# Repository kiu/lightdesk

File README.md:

# lightdesk

Custom desk light and RGB strip controller

Superseded by [https://github.com/kiu/kha](https://github.com/kiu/kha)

## Photos

## Render

# License

This project is licensed under the Creative Commons Attribution-NonCommercial 3.0 Unported (CC BY-NC 3.0) license.

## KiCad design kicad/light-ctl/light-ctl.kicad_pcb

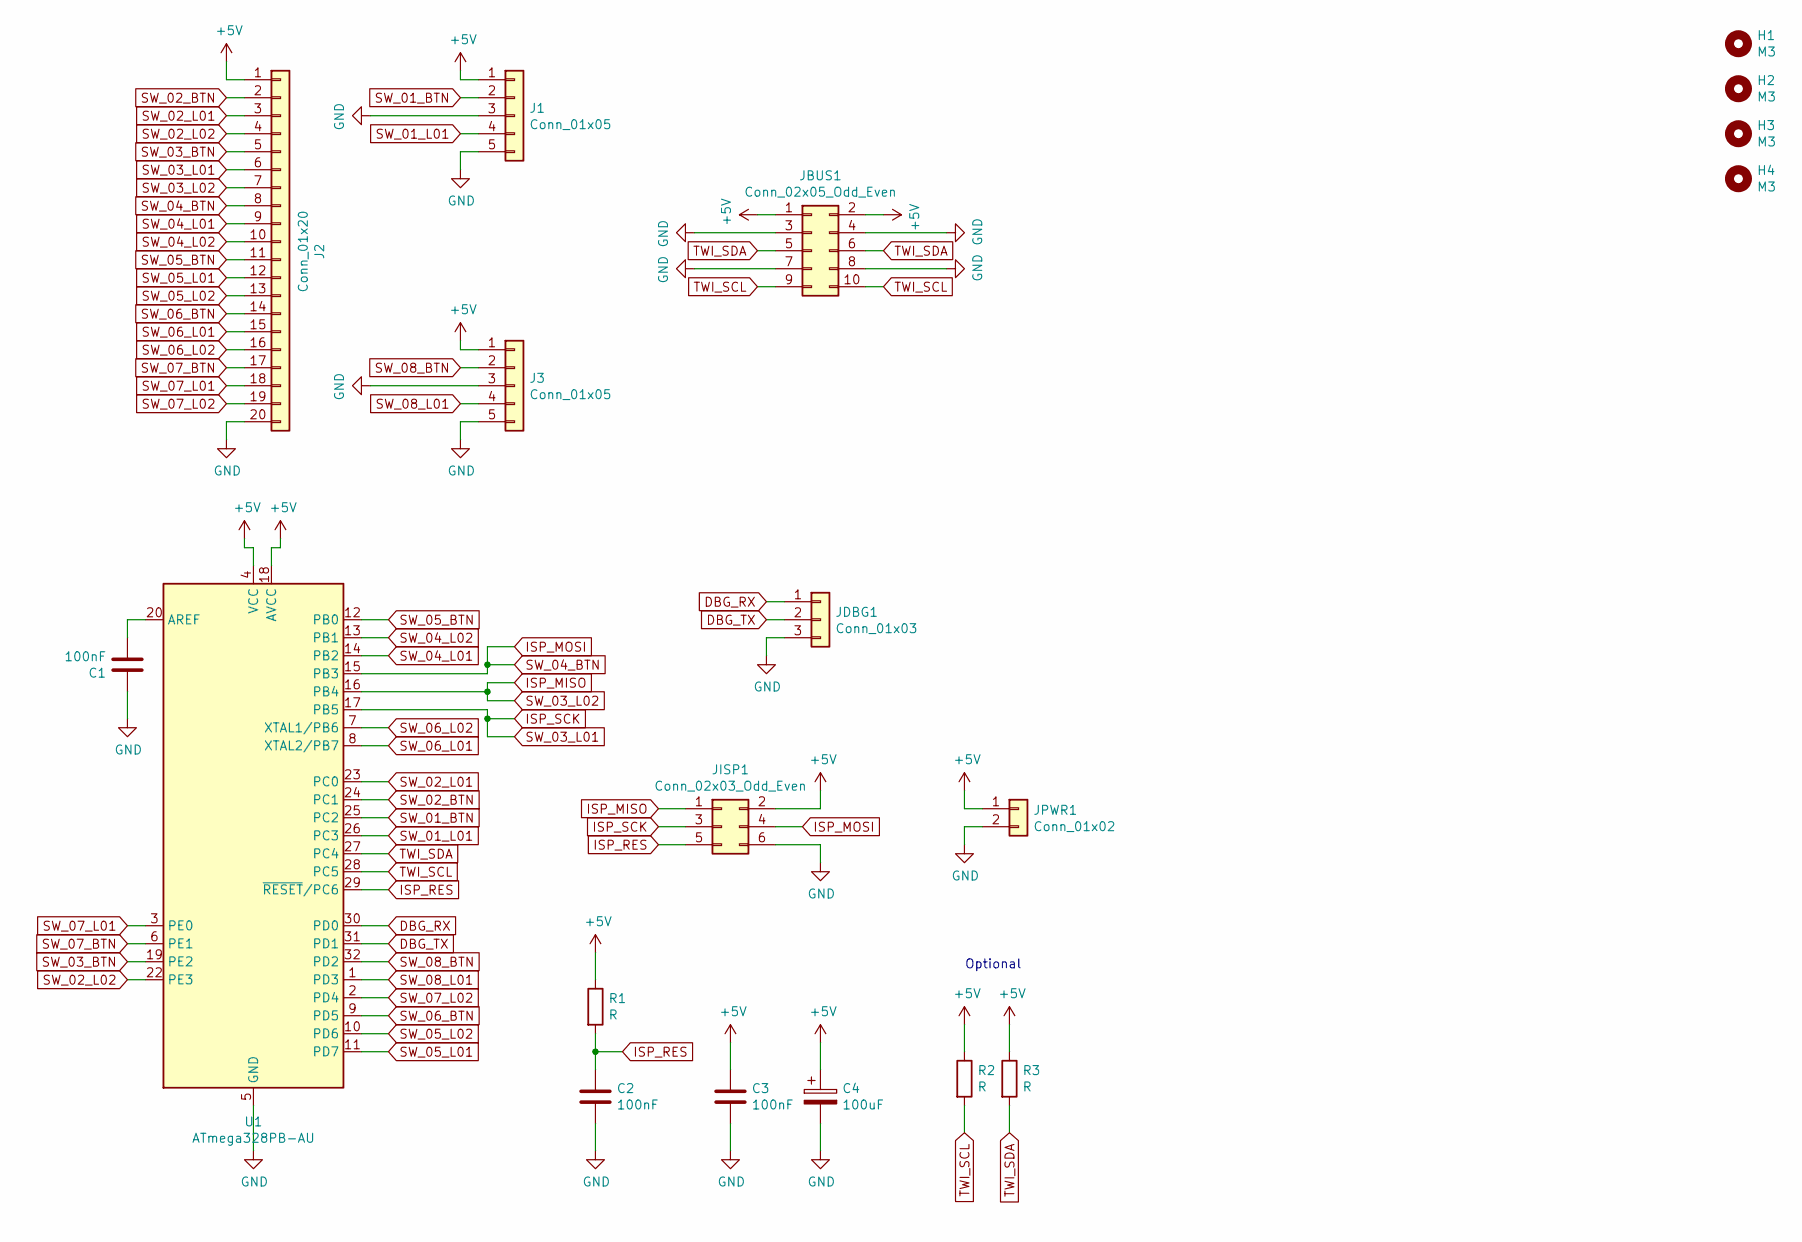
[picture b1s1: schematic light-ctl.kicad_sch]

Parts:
C1, C2, C3: 100nF; C_0805_HandSoldering
C4: 100uF; CP_Tantalum_Case-B_EIA-3528-21_Hand
H1, H2, H3, H4: M3; MountingHole_3.2mm_M3_DIN965
J1, J3: Conn_01x05; Pin_Header_Straight_1x05_Pitch2.54mm
J2: Conn_01x20; Pin_Header_Straight_1x20_Pitch2.54mm
JBUS1: Conn_02x05_Odd_Even; Pin_Header_Straight_2x05_Pitch2.54mm
JDBG1: Conn_01x03; Pin_Header_Straight_1x03_Pitch2.54mm
JISP1: Conn_02x03_Odd_Even; Pin_Header_Straight_2x03_Pitch2.54mm
JPWR1: Conn_01x02; Pin_Header_Straight_1x02_Pitch2.54mm
R1, R2, R3: R; R_0805_HandSoldering
U1: ATmega328PB-AU; LQFP-32_7x7mm_Pitch0.8mm

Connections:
+5V: C3.1, C4.1, J1.1, J2.1, J3.1, JBUS1.1, JBUS1.2, JISP1.2, JPWR1.1, R1.1, R2.1, R3.1, U1.4 (VCC), U1.18 (AVCC)
DBG_RX: JDBG1.1, U1.30 (PD0)
DBG_TX: JDBG1.2, U1.31 (PD1)
GND: C1.1, C2.2, C3.2, C4.2, J1.3, J1.5, J2.20, J3.3, J3.5, JBUS1.3, JBUS1.4, JBUS1.7, JBUS1.8, JDBG1.3, JISP1.6, JPWR1.2, U1.5 (GND), U1.21 (GND)
ISP_MISO: J2.7, JISP1.1, U1.16 (PB4)
ISP_MOSI: J2.8, JISP1.4, U1.15 (PB3)
ISP_RES: C2.1, JISP1.5, R1.2, U1.29 (~RESET/PC6)
ISP_SCK: J2.6, JISP1.3, U1.17 (PB5)
unnamed: C1.2, U1.20 (AREF)
SW_01_BTN: J1.2, U1.25 (PC2)
SW_01_L01: J1.4, U1.26 (PC3)
SW_02_BTN: J2.2, U1.24 (PC1)
SW_02_L01: J2.3, U1.23 (PC0)
SW_02_L02: J2.4, U1.22 (PE3)
SW_03_BTN: J2.5, U1.19 (PE2)
SW_04_L01: J2.9, U1.14 (PB2)
SW_04_L02: J2.10, U1.13 (PB1)
SW_05_BTN: J2.11, U1.12 (PB0)
SW_05_L01: J2.12, U1.11 (PD7)
SW_05_L02: J2.13, U1.10 (PD6)
SW_06_BTN: J2.14, U1.9 (PD5)
SW_06_L01: J2.15, U1.8 (XTAL2/PB7)
SW_06_L02: J2.16, U1.7 (XTAL1/PB6)
SW_07_BTN: J2.17, U1.6 (PE1)
SW_07_L01: J2.18, U1.3 (PE0)
SW_07_L02: J2.19, U1.2 (PD4)
SW_08_BTN: J3.2, U1.32 (PD2)
SW_08_L01: J3.4, U1.1 (PD3)
TWI_SCL: JBUS1.9, JBUS1.10, R2.2, U1.28 (PC5)
TWI_SDA: JBUS1.5, JBUS1.6, R3.2, U1.27 (PC4)

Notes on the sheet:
Optional

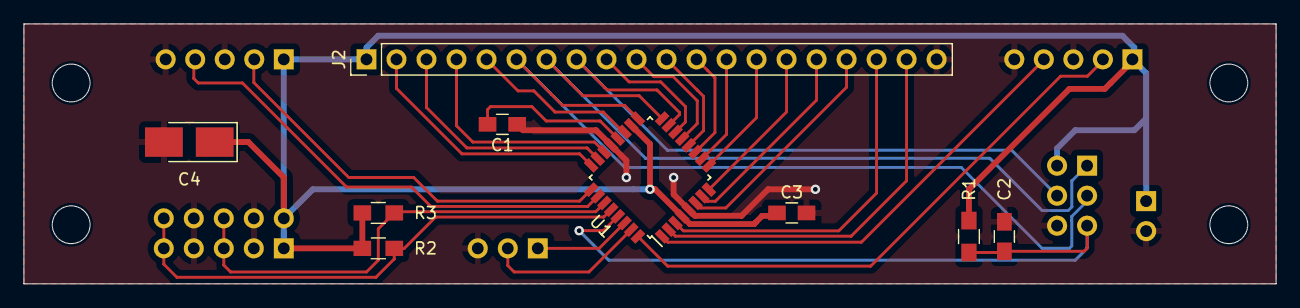
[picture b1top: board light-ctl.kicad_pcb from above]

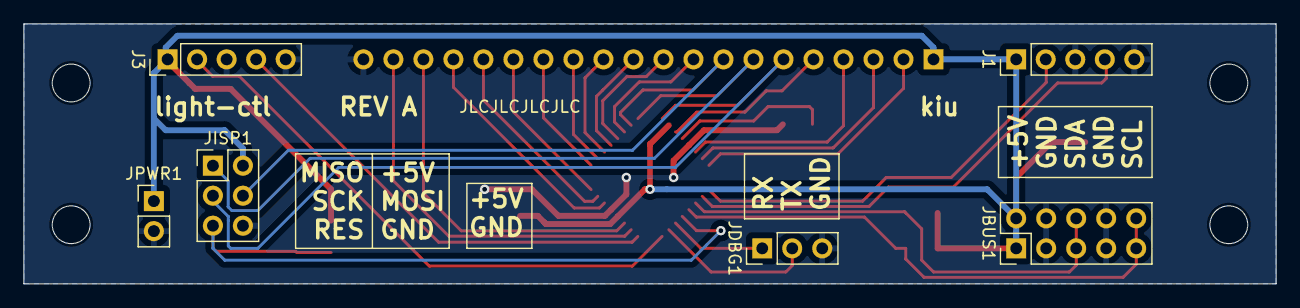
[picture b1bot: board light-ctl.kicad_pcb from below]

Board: 2 copper layers, 106.0 x 22.0 mm, 19 parts (6 on the bottom side), 30 nets.

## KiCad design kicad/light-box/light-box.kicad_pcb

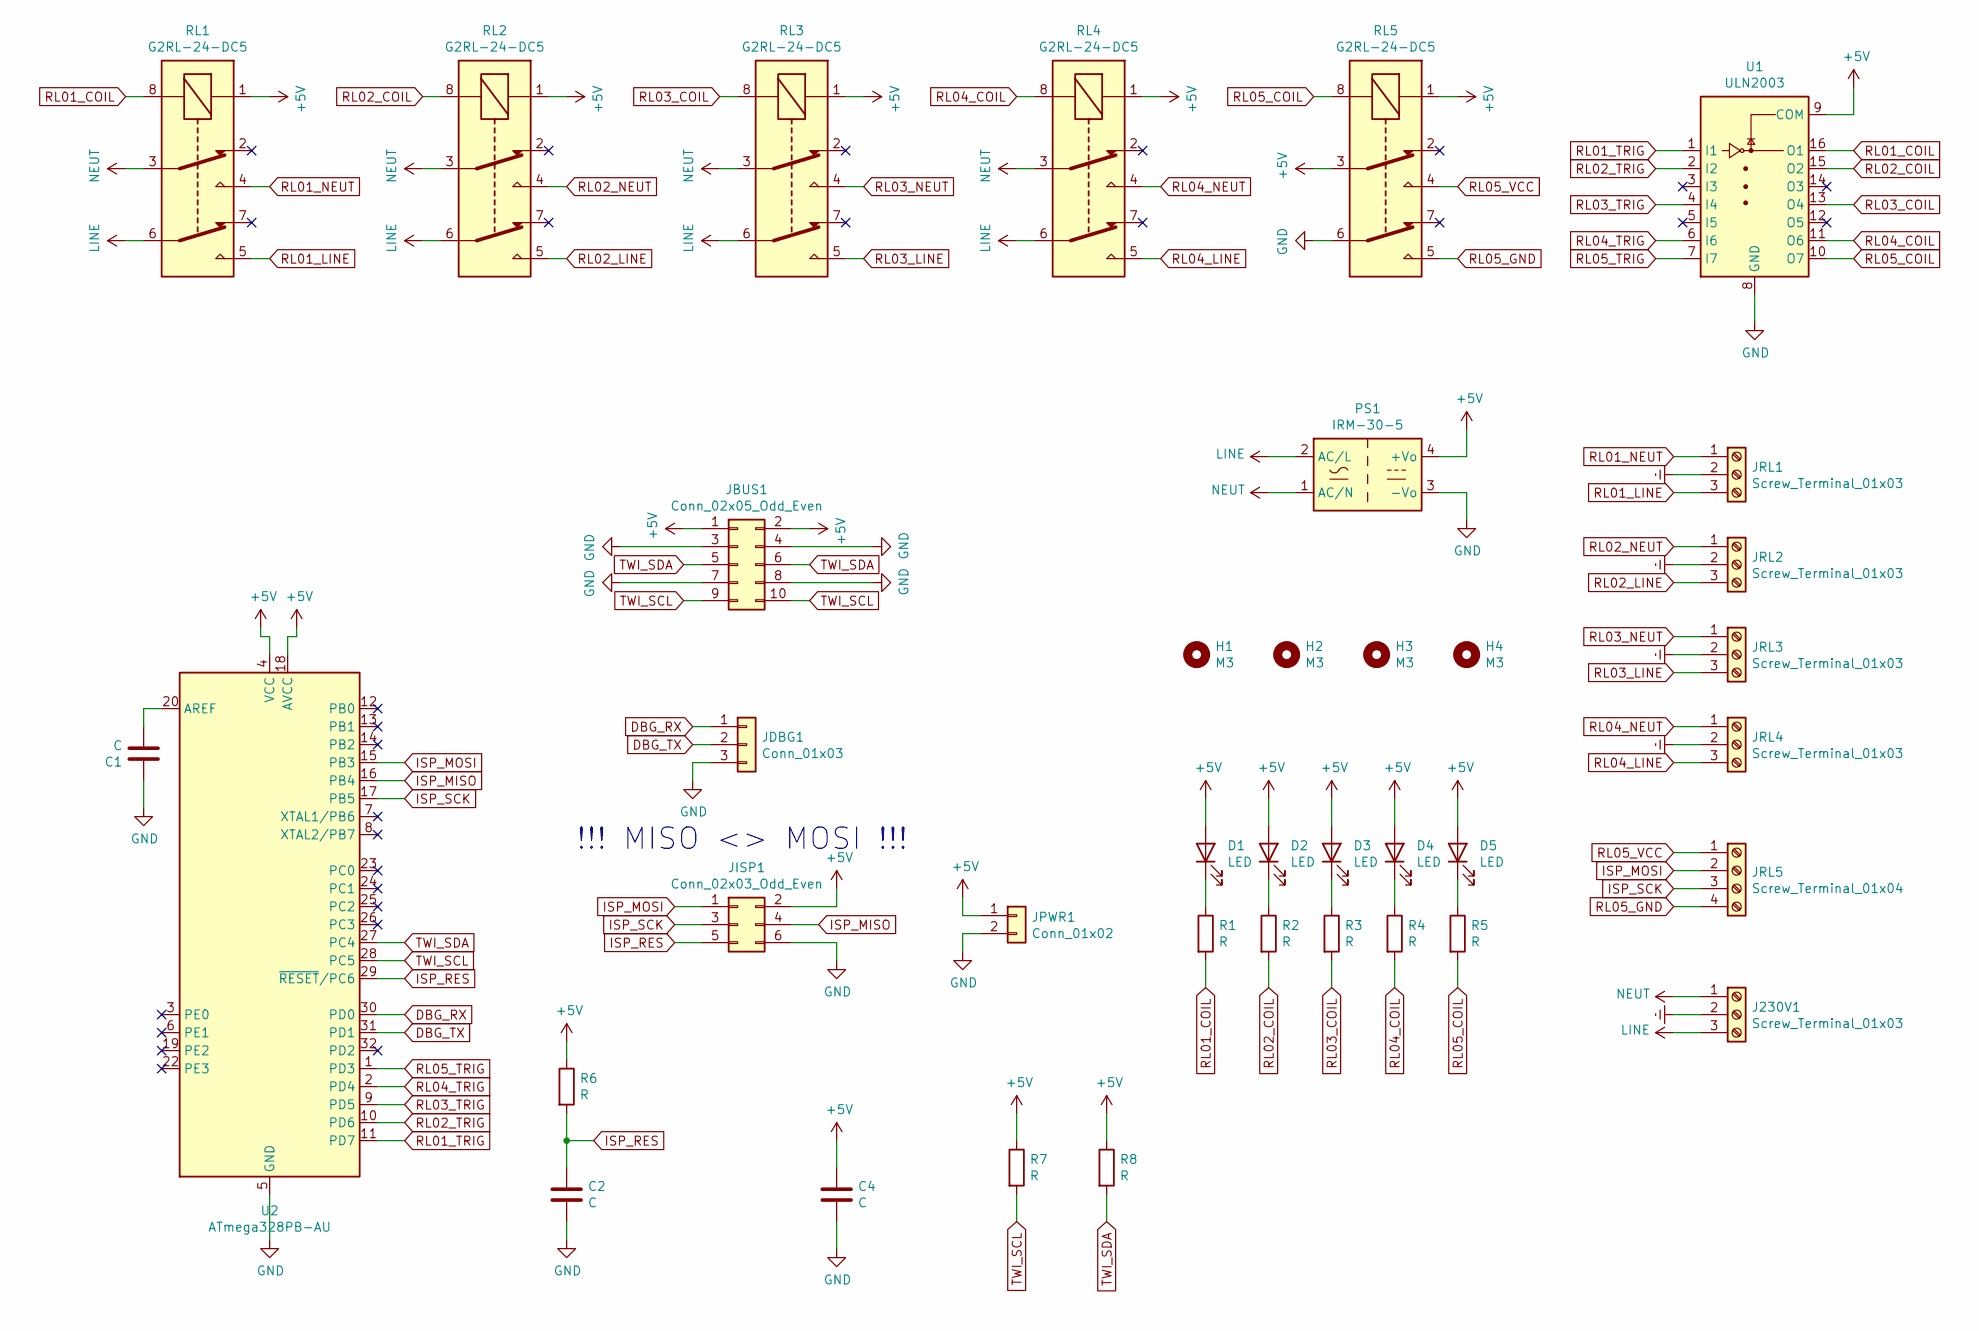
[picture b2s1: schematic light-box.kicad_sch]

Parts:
C1, C2, C4: C; C_0805_HandSoldering
D1, D2, D3, D4, D5: LED; LED_0805_HandSoldering
H1, H2, H3, H4: M3; MountingHole_3.2mm_M3_DIN965
J230V1: Screw_Terminal_01x03; TerminalBlock_bornier-3_P5.08mm
JBUS1: Conn_02x05_Odd_Even; Pin_Header_Straight_2x05_Pitch2.54mm
JDBG1: Conn_01x03; Pin_Header_Straight_1x03_Pitch2.54mm
JISP1: Conn_02x03_Odd_Even; Pin_Header_Straight_2x03_Pitch2.54mm
JPWR1: Conn_01x02; Pin_Header_Straight_1x02_Pitch2.54mm
JRL1, JRL2, JRL3, JRL4: Screw_Terminal_01x03; TerminalBlock_bornier-3_P5.08mm
JRL5: Screw_Terminal_01x04; TerminalBlock_bornier-4_P5.08mm
PS1: IRM-30-5; ACDC-Conv_MeanWell-IRM-30-XX
R1, R2, R3, R4, R5, R6, R7, R8: R; R_0805_HandSoldering
RL1, RL2, RL3, RL4, RL5: G2RL-24-DC5; Relay_DPDT_Omron_G2RL-24
U1: ULN2003; SOIC-16_3.9x9.9mm_Pitch1.27mm
U2: ATmega328PB-AU; TQFP-32_7x7mm_Pitch0.8mm

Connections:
+5V: C4.1, D1.2 (A), D2.2 (A), D3.2 (A), D4.2 (A), D5.2 (A), JBUS1.1, JBUS1.2, JISP1.2, JPWR1.1, PS1.4 (+Vo), R6.1, R7.1, R8.1, RL1.1, RL2.1, RL3.1, RL4.1, RL5.1, RL5.3, U1.9 (COM), U2.4 (VCC), U2.18 (AVCC)
DBG_RX: JDBG1.1, U2.30 (PD0)
DBG_TX: JDBG1.2, U2.31 (PD1)
Earth: J230V1.2, JRL1.2, JRL2.2, JRL3.2, JRL4.2
GND: C1.1, C2.2, C4.2, JBUS1.3, JBUS1.4, JBUS1.7, JBUS1.8, JDBG1.3, JISP1.6, JPWR1.2, PS1.3 (-Vo), RL5.6, U1.8 (GND), U2.5 (GND), U2.21 (GND)
ISP_MISO: JISP1.4, U2.16 (PB4)
ISP_MOSI: JISP1.1, JRL5.2, U2.15 (PB3)
ISP_RES: C2.1, JISP1.5, R6.2, U2.29 (~RESET/PC6)
ISP_SCK: JISP1.3, JRL5.3, U2.17 (PB5)
LINE: J230V1.3, PS1.2 (AC/L), RL1.6, RL2.6, RL3.6, RL4.6
NEUT: J230V1.1, PS1.1 (AC/N), RL1.3, RL2.3, RL3.3, RL4.3
unnamed: C1.2, U2.20 (AREF)
unnamed: D1.1 (K), R1.1
unnamed: D2.1 (K), R2.1
unnamed: D3.1 (K), R3.1
unnamed: D4.1 (K), R4.1
unnamed: D5.1 (K), R5.1
RL01_COIL: R1.2, RL1.8, U1.16 (O1)
RL01_LINE: JRL1.3, RL1.5
RL01_NEUT: JRL1.1, RL1.4
RL01_TRIG: U1.1 (I1), U2.11 (PD7)
RL02_COIL: R2.2, RL2.8, U1.15 (O2)
RL02_LINE: JRL2.3, RL2.5
RL02_NEUT: JRL2.1, RL2.4
RL02_TRIG: U1.2 (I2), U2.10 (PD6)
RL03_COIL: R3.2, RL3.8, U1.13 (O4)
RL03_LINE: JRL3.3, RL3.5
RL03_NEUT: JRL3.1, RL3.4
RL03_TRIG: U1.4 (I4), U2.9 (PD5)
RL04_COIL: R4.2, RL4.8, U1.11 (O6)
RL04_LINE: JRL4.3, RL4.5
RL04_NEUT: JRL4.1, RL4.4
RL04_TRIG: U1.6 (I6), U2.2 (PD4)
RL05_COIL: R5.2, RL5.8, U1.10 (O7)
RL05_GND: JRL5.4, RL5.5
RL05_TRIG: U1.7 (I7), U2.1 (PD3)
RL05_VCC: JRL5.1, RL5.4
TWI_SCL: JBUS1.9, JBUS1.10, R7.2, U2.28 (PC5)
TWI_SDA: JBUS1.5, JBUS1.6, R8.2, U2.27 (PC4)

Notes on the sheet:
!!! MISO <> MOSI !!!

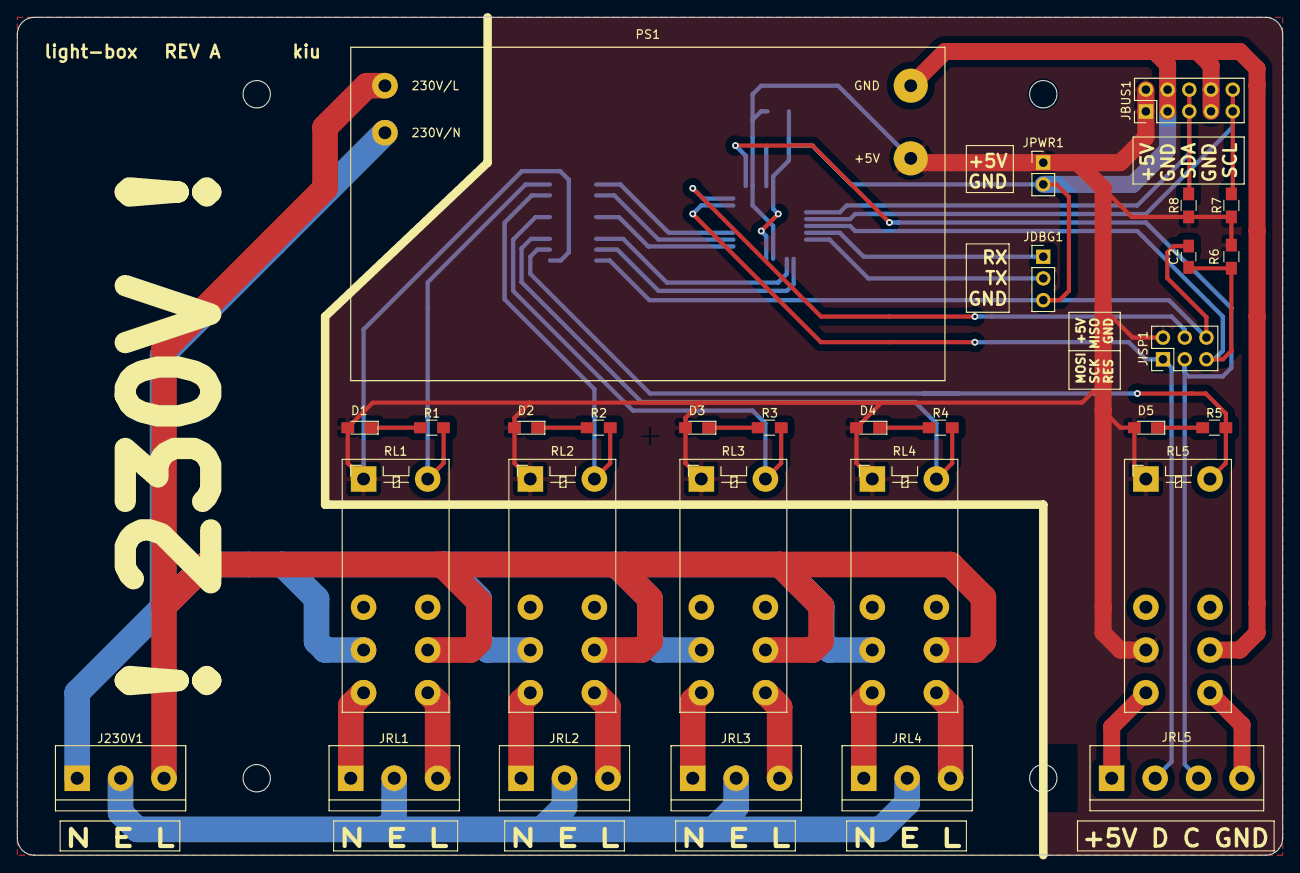
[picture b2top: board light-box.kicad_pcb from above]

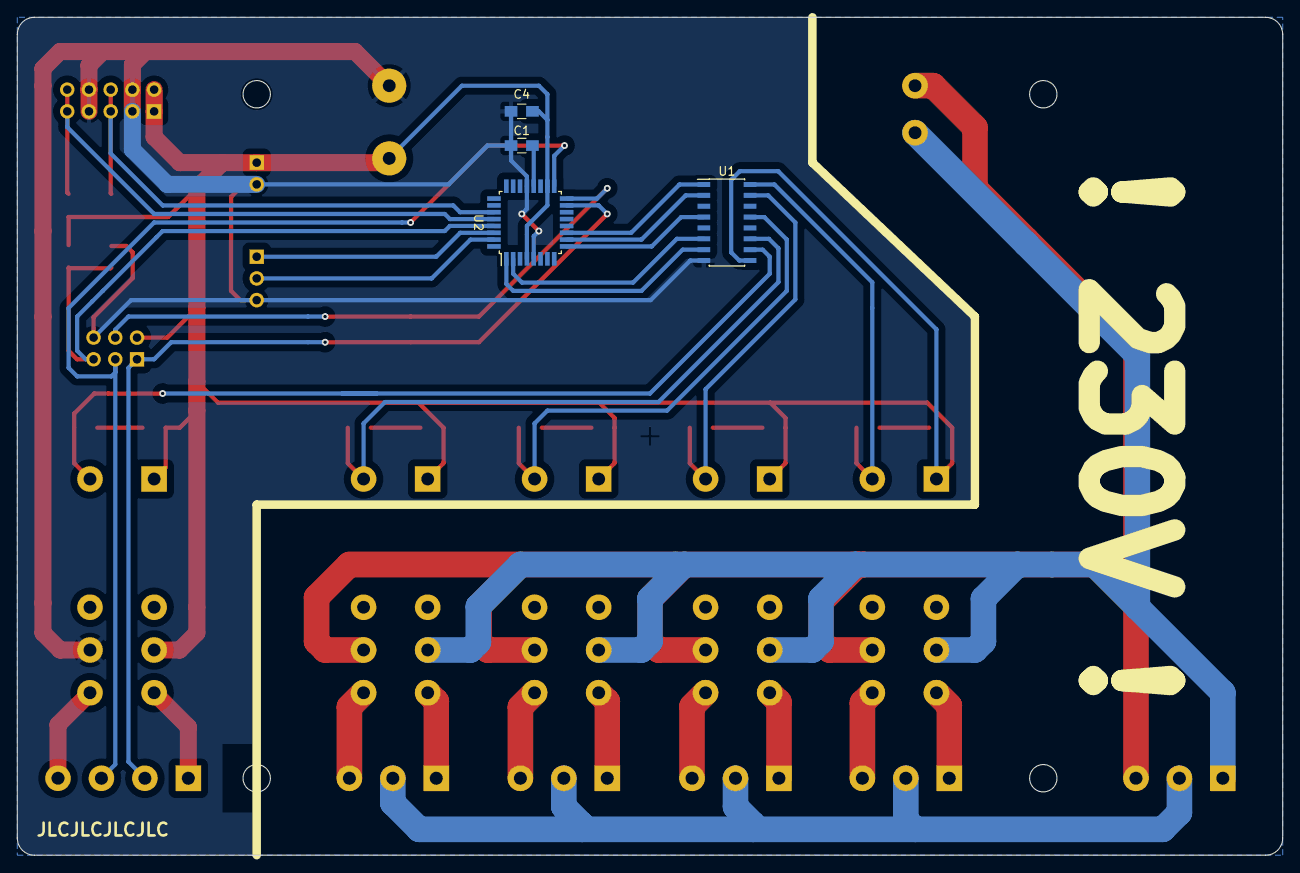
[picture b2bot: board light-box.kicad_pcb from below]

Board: 2 copper layers, 148.0 x 98.0 mm, 38 parts (4 on the bottom side), 39 nets.

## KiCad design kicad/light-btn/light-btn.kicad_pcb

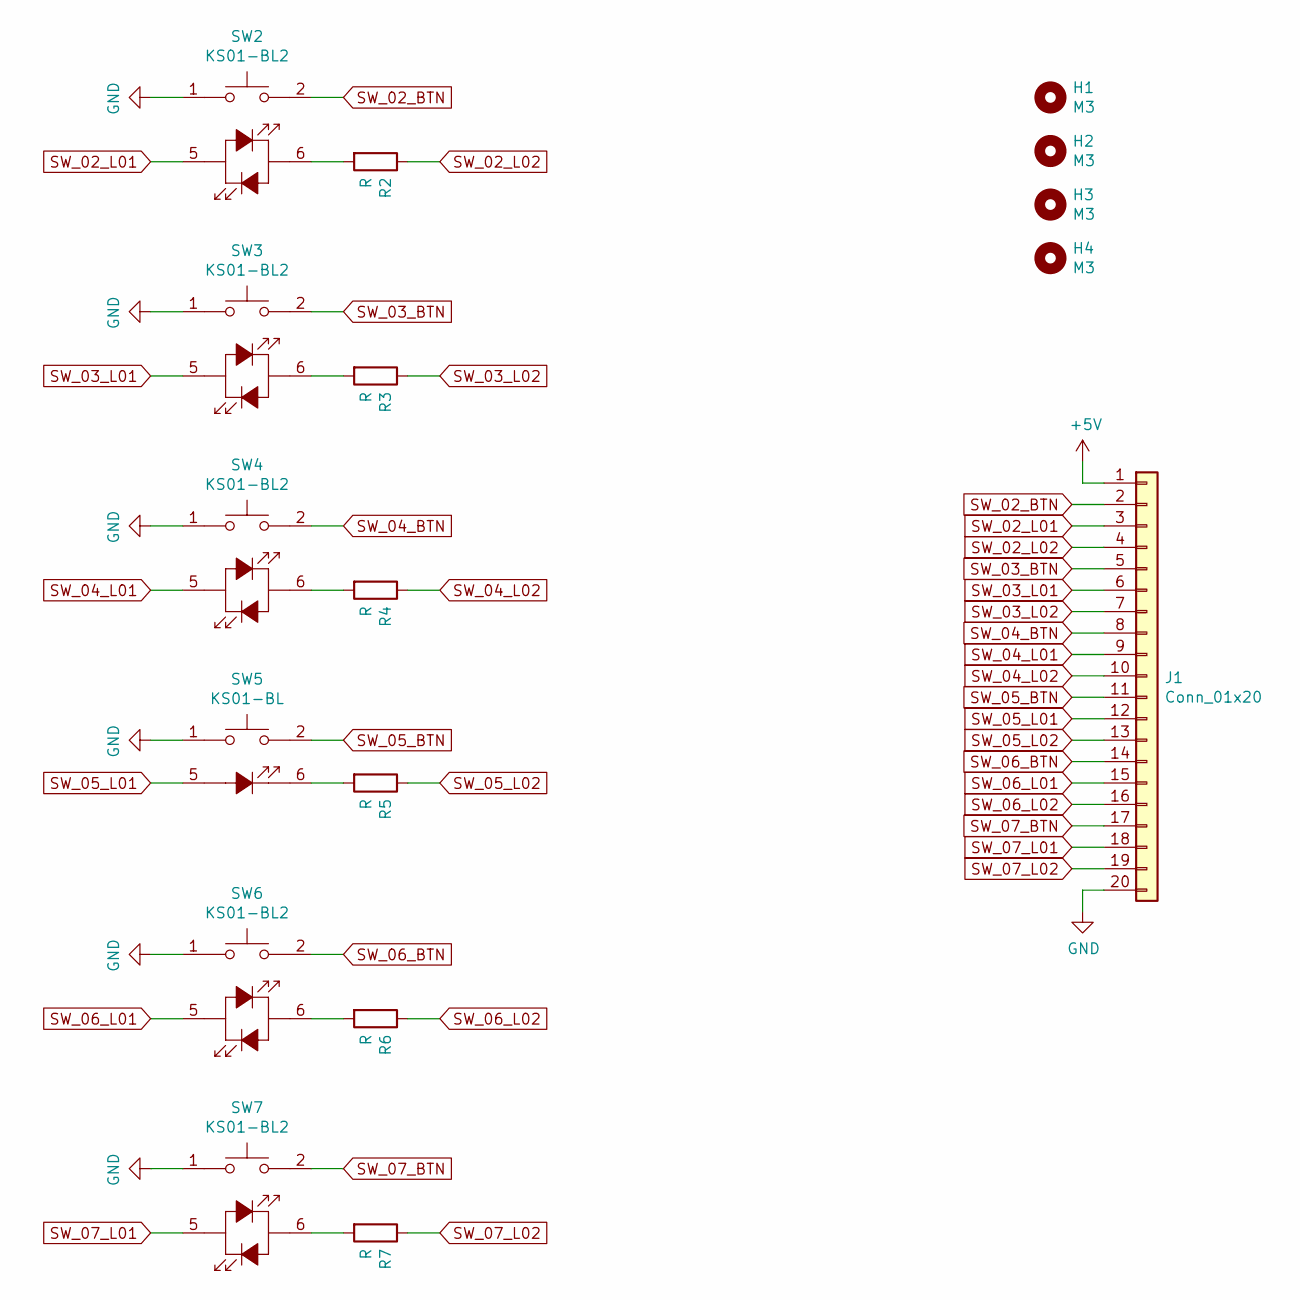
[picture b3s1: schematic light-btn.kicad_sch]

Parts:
H1, H2, H3, H4: M3; MountingHole_3.2mm_M3_DIN965
J1: Conn_01x20; Pin_Header_Straight_1x20_Pitch2.54mm
R2, R3, R4, R5, R6, R7: R; R_0805_HandSoldering
SW2, SW3, SW4, SW6, SW7: KS01-BL2; KS01-BL
SW5: KS01-BL

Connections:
GND: J1.20, SW2.1, SW3.1, SW4.1, SW5.1, SW6.1, SW7.1
unnamed: R2.2, SW2.6
unnamed: R3.2, SW3.6
unnamed: R4.2, SW4.6
unnamed: R5.2, SW5.6
unnamed: R6.2, SW6.6
unnamed: R7.2, SW7.6
SW_02_BTN: J1.2, SW2.2
SW_02_L01: J1.3, SW2.5
SW_02_L02: J1.4, R2.1
SW_03_BTN: J1.5, SW3.2
SW_03_L01: J1.6, SW3.5
SW_03_L02: J1.7, R3.1
SW_04_BTN: J1.8, SW4.2
SW_04_L01: J1.9, SW4.5
SW_04_L02: J1.10, R4.1
SW_05_BTN: J1.11, SW5.2
SW_05_L01: J1.12, SW5.5
SW_05_L02: J1.13, R5.1
SW_06_BTN: J1.14, SW6.2
SW_06_L01: J1.15, SW6.5
SW_06_L02: J1.16, R6.1
SW_07_BTN: J1.17, SW7.2
SW_07_L01: J1.18, SW7.5
SW_07_L02: J1.19, R7.1

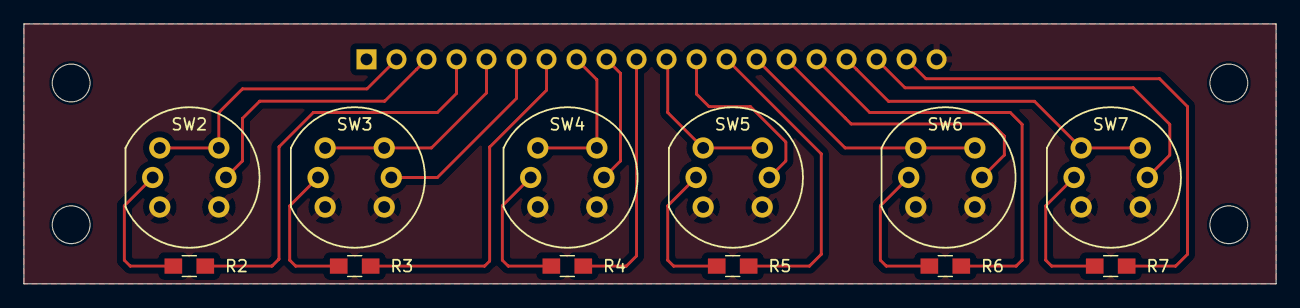
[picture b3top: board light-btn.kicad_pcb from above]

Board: 2 copper layers, 106.0 x 22.0 mm, 17 parts (1 on the bottom side), 25 nets.

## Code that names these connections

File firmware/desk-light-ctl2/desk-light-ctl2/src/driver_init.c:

/**
 * \file
 *
 * \brief Driver initialization.
 *
 (c) 2020 Microchip Technology Inc. and its subsidiaries.

    Subject to your compliance with these terms,you may use this software and
    any derivatives exclusively with Microchip products.It is your responsibility
    to comply with third party license terms applicable to your use of third party
    software (including open source software) that may accompany Microchip software.

    THIS SOFTWARE IS SUPPLIED BY MICROCHIP "AS IS". NO WARRANTIES, WHETHER
    EXPRESS, IMPLIED OR STATUTORY, APPLY TO THIS SOFTWARE, INCLUDING ANY IMPLIED
    WARRANTIES OF NON-INFRINGEMENT, MERCHANTABILITY, AND FITNESS FOR A
    PARTICULAR PURPOSE.

    IN NO EVENT WILL MICROCHIP BE LIABLE FOR ANY INDIRECT, SPECIAL, PUNITIVE,
    INCIDENTAL OR CONSEQUENTIAL LOSS, DAMAGE, COST OR EXPENSE OF ANY KIND
    WHATSOEVER RELATED TO THE SOFTWARE, HOWEVER CAUSED, EVEN IF MICROCHIP HAS
    BEEN ADVISED OF THE POSSIBILITY OR THE DAMAGES ARE FORESEEABLE. TO THE
    FULLEST EXTENT ALLOWED BY LAW, MICROCHIP'S TOTAL LIABILITY ON ALL CLAIMS IN
    ANY WAY RELATED TO THIS SOFTWARE WILL NOT EXCEED THE AMOUNT OF FEES, IF ANY,
    THAT YOU HAVE PAID DIRECTLY TO MICROCHIP FOR THIS SOFTWARE.
 *
 */

/*
 * Code generated by START.
 *
 * This file will be overwritten when reconfiguring your START project.
 * Please copy examples or other code you want to keep to a separate file
 * to avoid losing it when reconfiguring.
 */

#include "driver_init.h"
#include <system.h>

/* configure pins and initialize registers */
void I2C_0_initialization(void)
{

	PC5_set_dir(
	    // <y> Pin direction
	    // <id> pad_dir
	    // <PORT_DIR_OFF"> Off
	    // <PORT_DIR_IN"> In
	    // <PORT_DIR_OUT"> Out
	    PORT_DIR_OUT);

	PC5_set_level(
	    // <y> Initial level
	    // <id> pad_initial_level
	    // <false"> Low
	    // <true"> High
	    false);

	PC5_set_pull_mode(
	    // <y> Pull configuration
	    // <id> pad_pull_config
	    // <PORT_PULL_OFF"> Off
	    // <PORT_PULL_UP"> Pull-up
	    PORT_PULL_OFF);

	PC4_set_dir(
	    // <y> Pin direction
	    // <id> pad_dir
	    // <PORT_DIR_OFF"> Off
	    // <PORT_DIR_IN"> In
	    // <PORT_DIR_OUT"> Out
	    PORT_DIR_OUT);

	PC4_set_level(
	    // <y> Initial level
	    // <id> pad_initial_level
	    // <false"> Low
	    // <true"> High
	    false);

	PC4_set_pull_mode(
	    // <y> Pull configuration
	    // <id> pad_pull_config
	    // <PORT_PULL_OFF"> Off
	    // <PORT_PULL_UP"> Pull-up
	    PORT_PULL_OFF);

	I2C_0_init();
}

void TIMER_0_initialization(void)
{

	TIMER_0_init();
}

void TIMER_1_initialization(void)
{

	TIMER_1_init();
}

void TIMER_2_initialization(void)
{

	TIMER_2_init();
}

/* configure pins and initialize registers */
void USART_0_initialization(void)
{

	// Set pin direction to input
	PD0_set_dir(PORT_DIR_IN);

	PD0_set_pull_mode(
	    // <y> Pull configuration
	    // <id> pad_pull_config
	    // <PORT_PULL_OFF"> Off
	    // <PORT_PULL_UP"> Pull-up
	    PORT_PULL_OFF);

	// Set pin direction to output
	PD1_set_dir(PORT_DIR_OUT);

	PD1_set_level(
	    // <y> Initial level
	    // <id> pad_initial_level
	    // <false"> Low
	    // <true"> High
	    false);

	USART_0_init();
}

/**
 * \brief System initialization
 */
void system_init()
{
	mcu_init();

	/* PORT setting on PB0 */

	// Set pin direction to input
	SW_05_BTN_set_dir(PORT_DIR_IN);

	SW_05_BTN_set_pull_mode(
	    // <y> Pull configuration
	    // <id> pad_pull_config
	    // <PORT_PULL_OFF"> Off
	    // <PORT_PULL_UP"> Pull-up
	    PORT_PULL_UP);

	/* PORT setting on PB1 */

	// Set pin direction to output
	SW_04_L02_set_dir(PORT_DIR_OUT);

	SW_04_L02_set_level(
	    // <y> Initial level
	    // <id> pad_initial_level
	    // <false"> Low
	    // <true"> High
	    false);

	/* PORT setting on PB2 */

	// Set pin direction to output
	SW_04_L01_set_dir(PORT_DIR_OUT);

	SW_04_L01_set_level(
	    // <y> Initial level
	    // <id> pad_initial_level
	    // <false"> Low
	    // <true"> High
	    false);

	/* PORT setting on PB3 */

	// Set pin direction to input
	SW_04_BTN_set_dir(PORT_DIR_IN);

	SW_04_BTN_set_pull_mode(
	    // <y> Pull configuration
	    // <id> pad_pull_config
	    // <PORT_PULL_OFF"> Off
	    // <PORT_PULL_UP"> Pull-up
	    PORT_PULL_UP);

	/* PORT setting on PB4 */

	// Set pin direction to output
	SW_03_L02_set_dir(PORT_DIR_OUT);

	SW_03_L02_set_level(
	    // <y> Initial level
	    // <id> pad_initial_level
	    // <false"> Low
	    // <true"> High
	    false);

	/* PORT setting on PB5 */

	// Set pin direction to output
	SW_03_L01_set_dir(PORT_DIR_OUT);

	SW_03_L01_set_level(
	    // <y> Initial level
	    // <id> pad_initial_level
	    // <false"> Low
	    // <true"> High
	    false);

	/* PORT setting on PB6 */

	// Set pin direction to output
	SW_06_L02_set_dir(PORT_DIR_OUT);

	SW_06_L02_set_level(
	    // <y> Initial level
	    // <id> pad_initial_level
	    // <false"> Low
	    // <true"> High
	    false);

	/* PORT setting on PB7 */

	// Set pin direction to output
	SW_06_L01_set_dir(PORT_DIR_OUT);

	SW_06_L01_set_level(
	    // <y> Initial level
	    // <id> pad_initial_level
	    // <false"> Low
	    // <true"> High
	    false);

	/* PORT setting on PC0 */

	// Set pin direction to output
	SW_02_L01_set_dir(PORT_DIR_OUT);

	SW_02_L01_set_level(
	    // <y> Initial level
	    // <id> pad_initial_level
	    // <false"> Low
	    // <true"> High
	    false);

	/* PORT setting on PC1 */

	// Set pin direction to input
	SW_02_BTN_set_dir(PORT_DIR_IN);

	SW_02_BTN_set_pull_mode(
	    // <y> Pull configuration
	    // <id> pad_pull_config
	    // <PORT_PULL_OFF"> Off
	    // <PORT_PULL_UP"> Pull-up
	    PORT_PULL_UP);

	/* PORT setting on PC2 */

	// Set pin direction to input
	SW_01_BTN_set_dir(PORT_DIR_IN);

	SW_01_BTN_set_pull_mode(
	    // <y> Pull configuration
	    // <id> pad_pull_config
	    // <PORT_PULL_OFF"> Off
	    // <PORT_PULL_UP"> Pull-up
	    PORT_PULL_UP);

	/* PORT setting on PC3 */

	// Set pin direction to output
	SW_01_L01_set_dir(PORT_DIR_OUT);

	SW_01_L01_set_level(
	    // <y> Initial level
	    // <id> pad_initial_level
	    // <false"> Low
	    // <true"> High
	    false);

	/* PORT setting on PD2 */

	// Set pin direction to input
	SW_08_BTN_set_dir(PORT_DIR_IN);

	SW_08_BTN_set_pull_mode(
	    // <y> Pull configuration
	    // <id> pad_pull_config
	    // <PORT_PULL_OFF"> Off
	    // <PORT_PULL_UP"> Pull-up
	    PORT_PULL_UP);

	/* PORT setting on PD3 */

	// Set pin direction to output
	SW_08_L01_set_dir(PORT_DIR_OUT);

	SW_08_L01_set_level(
	    // <y> Initial level
	    // <id> pad_initial_level
	    // <false"> Low
	    // <true"> High
	    false);

	/* PORT setting on PD4 */

	// Set pin direction to output
	SW_07_L02_set_dir(PORT_DIR_OUT);

	SW_07_L02_set_level(
	    // <y> Initial level
	    // <id> pad_initial_level
	    // <false"> Low
	    // <true"> High
	    false);

	/* PORT setting on PD5 */

	// Set pin direction to input
	SW_06_BTN_set_dir(PORT_DIR_IN);

	SW_06_BTN_set_pull_mode(
	    // <y> Pull configuration
	    // <id> pad_pull_config
	    // <PORT_PULL_OFF"> Off
	    // <PORT_PULL_UP"> Pull-up
	    PORT_PULL_UP);

	/* PORT setting on PD6 */

	// Set pin direction to output
	SW_05_L02_set_dir(PORT_DIR_OUT);

	SW_05_L02_set_level(
	    // <y> Initial level
	    // <id> pad_initial_level
	    // <false"> Low
	    // <true"> High
	    false);

	/* PORT setting on PD7 */

	// Set pin direction to output
	SW_05_L01_set_dir(PORT_DIR_OUT);

	SW_05_L01_set_level(
	    // <y> Initial level
	    // <id> pad_initial_level
	    // <false"> Low
	    // <true"> High
	    false);

	/* PORT setting on PE0 */

	// Set pin direction to output
	SW_07_L01_set_dir(PORT_DIR_OUT);

	SW_07_L01_set_level(
	    // <y> Initial level
	    // <id> pad_initial_level
	    // <false"> Low
	    // <true"> High
	    false);

	/* PORT setting on PE1 */

	// Set pin direction to input
	SW_07_BTN_set_dir(PORT_DIR_IN);

	SW_07_BTN_set_pull_mode(
	    // <y> Pull configuration
	    // <id> pad_pull_config
	    // <PORT_PULL_OFF"> Off
	    // <PORT_PULL_UP"> Pull-up
	    PORT_PULL_UP);

	/* PORT setting on PE2 */

	// Set pin direction to input
	SW_03_BTN_set_dir(PORT_DIR_IN);

	SW_03_BTN_set_pull_mode(
	    // <y> Pull configuration
	    // <id> pad_pull_config
	    // <PORT_PULL_OFF"> Off
	    // <PORT_PULL_UP"> Pull-up
	    PORT_PULL_UP);

	/* PORT setting on PE3 */

	// Set pin direction to output
	SW_02_L02_set_dir(PORT_DIR_OUT);

	SW_02_L02_set_level(
	    // <y> Initial level
	    // <id> pad_initial_level
	    // <false"> Low
	    // <true"> High
	    false);

	sysctrl_init();

	I2C_0_initialization();

	TIMER_0_initialization();

	TIMER_1_initialization();

	TIMER_2_initialization();

	USART_0_initialization();
}

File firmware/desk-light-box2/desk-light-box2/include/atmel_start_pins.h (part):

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#include <port.h>

/**
 * \brief Set PB3 pull mode
 *
 * Configure pin to pull up, down or disable pull mode, supported pull
 * modes are defined by device used
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}

/**
 * \brief Set PB3 data direction
 *
 * Select if the pin data direction is input, output or disabled.
 * If disabled state is not possible, this function throws an assert.
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}

/**
 * \brief Set PB3 level
 *
 * Sets output level on a pin
 *
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}

/**
 * \brief Toggle output level on PB3
 *
 * Toggle the pin level
 */
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}

/**
 * \brief Get level on PB3
 *
 * Reads the level on a pin
 */
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}

/**
 * \brief Set PB4 pull mode
 *
 * Configure pin to pull up, down or disable pull mode, supported pull
 * modes are defined by device used
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}

/**
 * \brief Set PB4 data direction
 *
 * Select if the pin data direction is input, output or disabled.
 * If disabled state is not possible, this function throws an assert.
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}

/**
 * \brief Set PB4 level
 *
 * Sets output level on a pin
 *
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}

/**
 * \brief Toggle output level on PB4
 *
 * Toggle the pin level
 */
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}

/**
 * \brief Get level on PB4
 *
 * Reads the level on a pin
 */
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}

/**
 * \brief Set PB5 pull mode
 *
 * Configure pin to pull up, down or disable pull mode, supported pull
 * modes are defined by device used
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}

/**
 * \brief Set PB5 data direction
 *
 * Select if the pin data direction is input, output or disabled.
 * If disabled state is not possible, this function throws an assert.
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}

/**
 * \brief Set PB5 level
 *
 * Sets output level on a pin
 *
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}

/**
 * \brief Toggle output level on PB5
 *
 * Toggle the pin level
 */
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}

/**
 * \brief Get level on PB5
 *
 * Reads the level on a pin
 */
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}

/**
 * \brief Set PC4 pull mode
 *
 * Configure pin to pull up, down or disable pull mode, supported pull
 * modes are defined by device used
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}

/**
 * \brief Set PC4 data direction
 *
 * Select if the pin data direction is input, output or disabled.
 * If disabled state is not possible, this function throws an assert.
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}

/**
 * \brief Set PC4 level
 *
 * Sets output level on a pin
 *
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}

/**
 * \brief Toggle output level on PC4
 *
 * Toggle the pin level
 */
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}

/**
 * \brief Get level on PC4
 *
 * Reads the level on a pin
 */
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}

/**
 * \brief Set PC5 pull mode
 *
 * Configure pin to pull up, down or disable pull mode, supported pull
 * modes are defined by device used
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}

/**
 * \brief Set PC5 data direction
 *
 * Select if the pin data direction is input, output or disabled.
 * If disabled state is not possible, this function throws an assert.
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}

/**
 * \brief Set PC5 level
 *
 * Sets output level on a pin
 *
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}

/**
 * \brief Toggle output level on PC5
 *
 * Toggle the pin level
 */
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}

/**
 * \brief Get level on PC5
 *
 * Reads the level on a pin
 */
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}

/**
 * \brief Set PD0 pull mode
 *
 * Configure pin to pull up, down or disable pull mode, supported pull
 * modes are defined by device used
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}

/**
 * \brief Set PD0 data direction
 *
 * Select if the pin data direction is input, output or disabled.
 * If disabled state is not possible, this function throws an assert.
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}

/**
 * \brief Set PD0 level
 *
 * Sets output level on a pin
 *
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}

/**
 * \brief Toggle output level on PD0
 *
 * Toggle the pin level
 */
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}

/**
 * \brief Get level on PD0
 *
 * Reads the level on a pin
 */
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}

/**
 * \brief Set PD1 pull mode
 *
 * Configure pin to pull up, down or disable pull mode, supported pull
 * modes are defined by device used
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}

/**
 * \brief Set PD1 data direction
 *
 * Select if the pin data direction is input, output or disabled.
 * If disabled state is not possible, this function throws an assert.
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}

/**
 * \brief Set PD1 level
 *
 * Sets output level on a pin
 *
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}

/**
 * \brief Toggle output level on PD1
 *
 * Toggle the pin level
 */
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}

/**
 * \brief Get level on PD1
 *
 * Reads the level on a pin
 */
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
